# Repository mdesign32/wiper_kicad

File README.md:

# Wiper

Печатная плата контроллера (ATmega, реле), KiCad 9.0.7.

| Файл | Назначение |
|---|---|
| `wiper.kicad_pro` | проект |
| `wiper.kicad_sch` | схема |
| `wiper.kicad_pcb` | печатная плата (2 слоя, 90 × 67,5 мм, 1,6 мм) |

Все символы и посадочные места взяты из стандартных библиотек KiCad 9.

Гербер-файлы изготовленных версий прикладываются к релизам на GitHub.

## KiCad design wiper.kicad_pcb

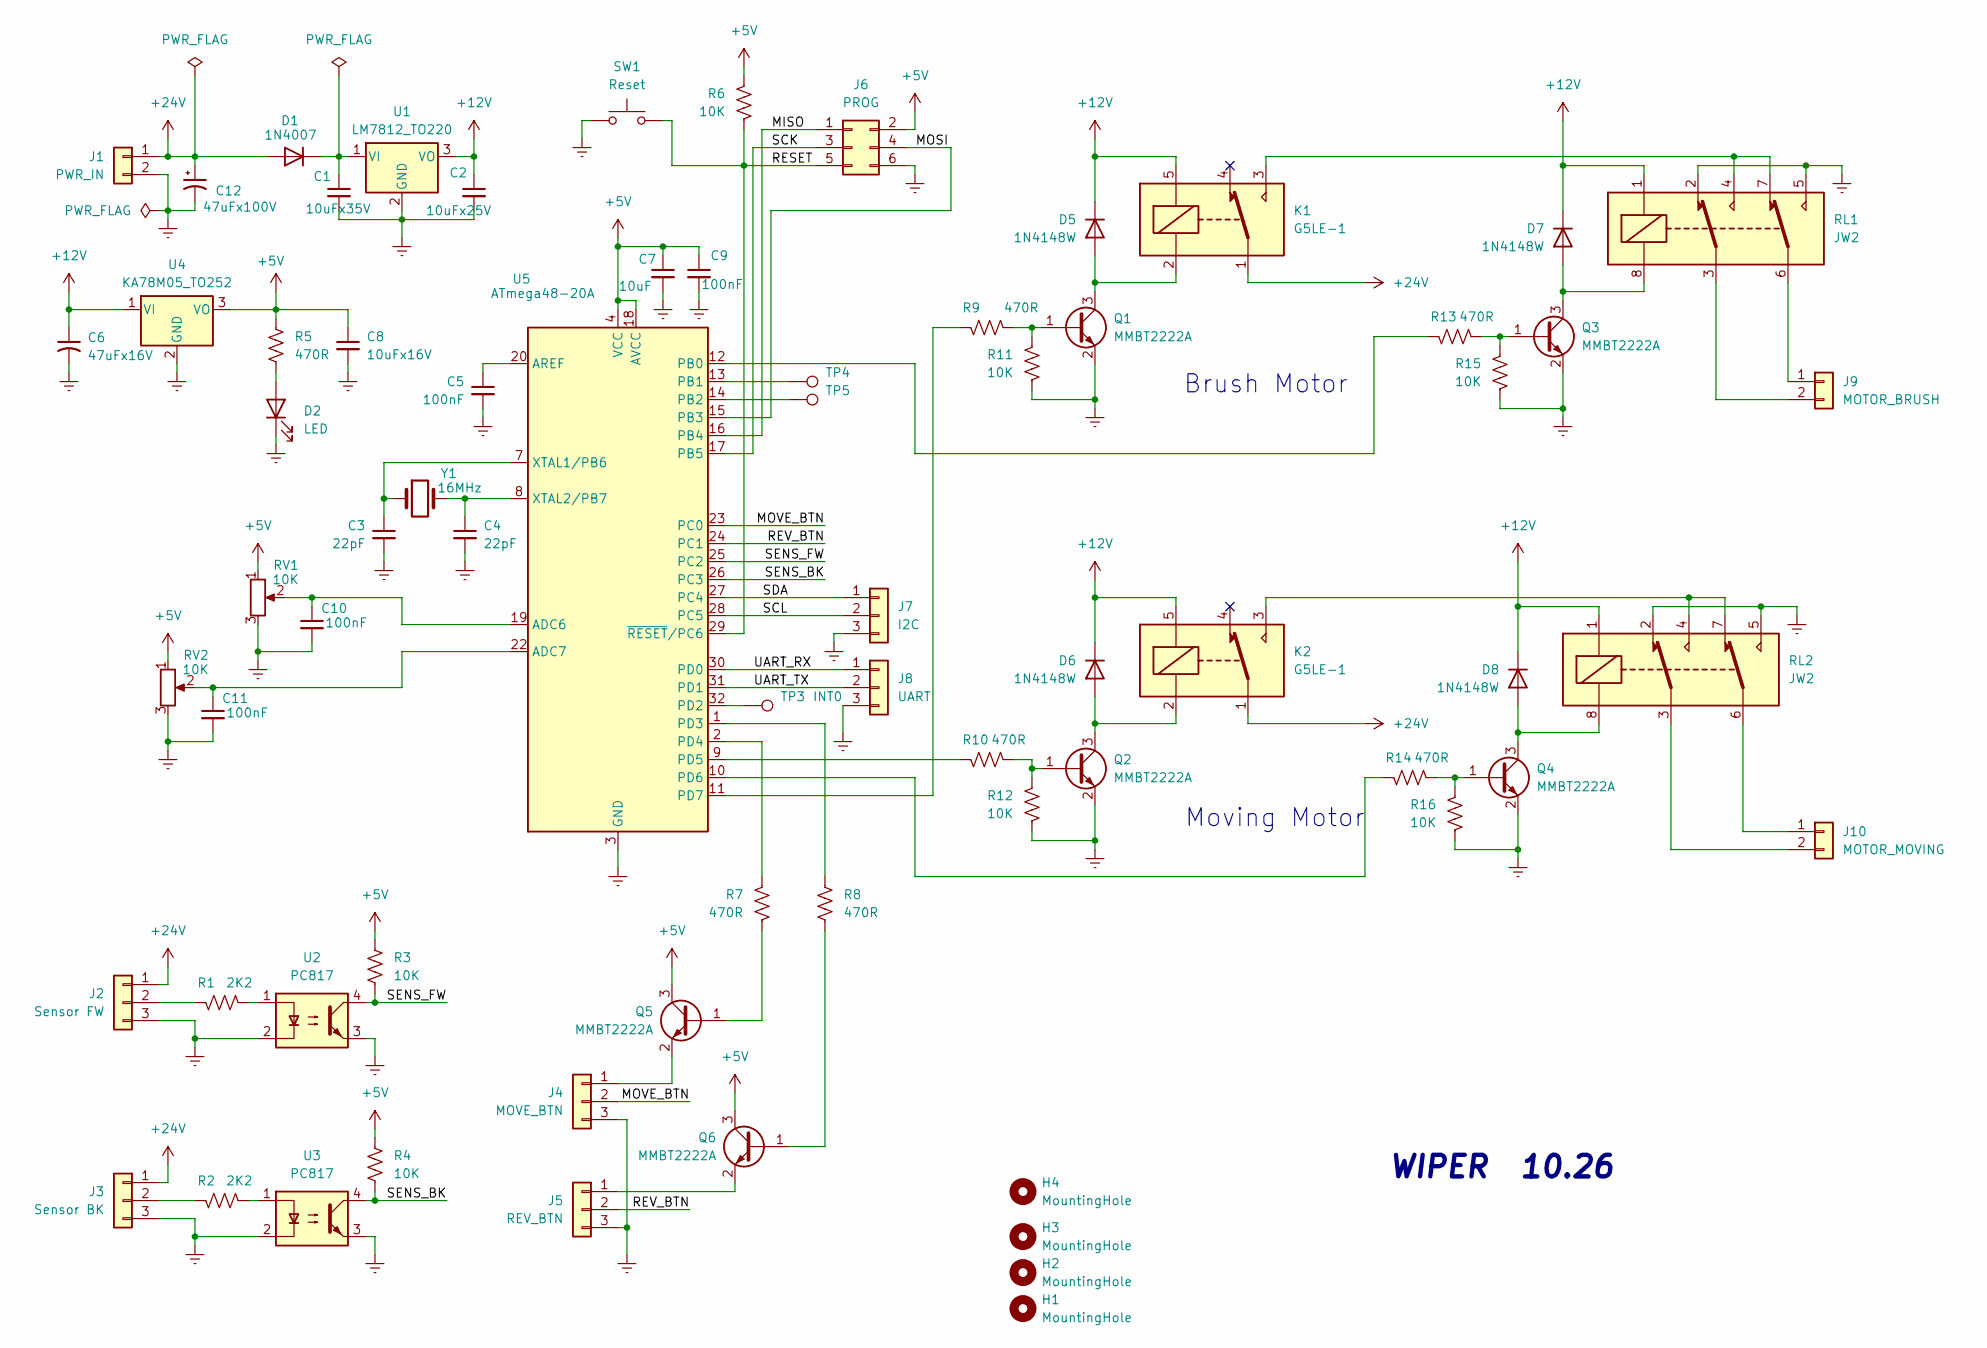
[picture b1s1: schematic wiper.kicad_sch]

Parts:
C1: 10uFx35V; C_1206_3216Metric
C2: 10uFx25V; C_1206_3216Metric
C3, C4: 22pF; C_0603_1608Metric_Pad1.08x0.95mm_HandSolder
C5, C10, C11: 100nF; C_0805_2012Metric_Pad1.18x1.45mm_HandSolder
C6: 47uFx16V; CP_EIA-7132-28_AVX-C_HandSolder
C7: 10uF; C_0805_2012Metric_Pad1.18x1.45mm_HandSolder
C8: 10uFx16V; C_0805_2012Metric_Pad1.18x1.45mm_HandSolder
C9: 100nF; C_0603_1608Metric_Pad1.08x0.95mm_HandSolder
C12: 47uFx100V; C_Radial_D8.0mm_H7.0mm_P3.50mm
D1: 1N4007; D_DO-41_SOD81_P10.16mm_Horizontal
D2: LED; LED_D3.0mm
D5, D6, D7, D8: 1N4148W; D_SOD-123
H1, H2, H3, H4: MountingHole; MountingHole_3.2mm_M3
J1: PWR_IN; TerminalBlock_MetzConnect_Type101_RT01602HBWC_1x02_P5.08mm_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
J2: Sensor FW; TerminalBlock_MetzConnect_Type055_RT01503HDWU_1x03_P5.00mm_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
J3: Sensor BK; TerminalBlock_MetzConnect_Type055_RT01503HDWU_1x03_P5.00mm_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
J4: MOVE_BTN; Molex_KK-254_AE-6410-03A_1x03_P2.54mm_Vertical
J5: REV_BTN; Molex_KK-254_AE-6410-03A_1x03_P2.54mm_Vertical
J6: PROG; PinHeader_2x03_P2.54mm_Vertical
J7: I2C; PinHeader_1x03_P2.54mm_Vertical
J8: UART; PinHeader_1x03_P2.54mm_Vertical
J9: MOTOR_BRUSH; TerminalBlock_MetzConnect_Type101_RT01602HBWC_1x02_P5.08mm_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
J10: MOTOR_MOVING; TerminalBlock_MetzConnect_Type101_RT01602HBWC_1x02_P5.08mm_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
K1, K2: G5LE-1; Relay_SPDT_Omron-G5LE-1
Q1, Q2, Q3, Q4, Q5, Q6: MMBT2222A; SOT-23
R1, R2: 2K2; R_0805_2012Metric_Pad1.20x1.40mm_HandSolder
R3, R4, R6, R11, R12, R15, R16: 10K; R_0805_2012Metric_Pad1.20x1.40mm_HandSolder
R5, R7, R8, R9, R10, R13, R14: 470R; R_0805_2012Metric_Pad1.20x1.40mm_HandSolder
RL1, RL2: JW2; Relay_DPDT_Panasonic_JW2
RV1, RV2: 10K; Potentiometer_Piher_PT-6-V_Vertical
SW1: Reset; SW_Push_1P1T_NO_E-Switch_TL3301NxxxxxG
TP3: INT0; PinHeader_1x01_P1.00mm_Vertical
TP4, TP5: PinHeader_1x01_P1.00mm_Vertical
U1: LM7812_TO220; TO-220-3_Vertical
U2, U3: PC817; DIP-4_W7.62mm
U4: KA78M05_TO252; TO-252-2
U5: ATmega48-20A; TQFP-32_7x7mm_P0.8mm
Y1: 16MHz; Crystal_HC49-4H_Vertical

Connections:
+5V: C7.1, C8.1, C9.1, J6.2, Q5.3 (C), Q6.3 (C), R3.1, R4.1, R5.1, R6.1, RV1.1, RV2.1, U4.3 (VO), U5.4 (VCC), U5.6 (VCC), U5.18 (AVCC)
+12V: C2.1, C6.1, D5.1 (K), D6.1 (K), D7.1 (K), D8.1 (K), K1.5, K2.5, RL1.1, RL2.1, U1.3 (VO), U4.1 (VI)
+24V: C12.1, D1.2 (A), J1.1, J2.1, J3.1, K1.1, K2.1
/MISO: J6.1, U5.16 (PB4)
/MOSI: J6.4, U5.15 (PB3)
/MOVE_BTN: J4.2, U5.23 (PC0)
/RESET: J6.5, R6.2, SW1.2, U5.29 (~RESET/PC6)
/REV_BTN: J5.2, U5.24 (PC1)
/SCK: J6.3, U5.17 (PB5)
/SCL: J7.2, U5.28 (PC5)
/SDA: J7.1, U5.27 (PC4)
/SENS_BK: R4.2, U3.4, U5.26 (PC3)
/SENS_FW: R3.2, U2.4, U5.25 (PC2)
/UART_RX: J8.1, U5.30 (PD0)
/UART_TX: J8.2, U5.31 (PD1)
unnamed: C1.1, D1.1 (K), U1.1 (VI)
unnamed: D2.2 (A), R5.2
unnamed: D5.2 (A), K1.2, Q1.3 (C)
unnamed: D6.2 (A), K2.2, Q2.3 (C)
unnamed: D7.2 (A), Q3.3 (C), RL1.8
unnamed: D8.2 (A), Q4.3 (C), RL2.8
unnamed: J2.2, R1.2
unnamed: J3.2, R2.2
unnamed: J4.1, Q5.2 (E)
unnamed: J5.1, Q6.2 (E)
unnamed: J9.1, RL1.6
unnamed: J9.2, RL1.3
unnamed: J10.1, RL2.6
unnamed: J10.2, RL2.3
unnamed: K1.3, RL1.4, RL1.7
unnamed: K2.3, RL2.4, RL2.7
unnamed: Q1.1 (B), R9.1, R11.1
unnamed: Q2.1 (B), R10.1, R12.1
unnamed: Q3.1 (B), R13.1, R15.1
unnamed: Q4.1 (B), R14.1, R16.1
unnamed: Q5.1 (B), R7.2
unnamed: Q6.1 (B), R8.2
unnamed: R1.1, U2.1
unnamed: R2.1, U3.1
unnamed: C10.1, RV1.2, U5.19 (ADC6)
unnamed: C11.1, RV2.2, U5.22 (ADC7)
unnamed: C5.1, U5.20 (AREF)
unnamed: R13.2, U5.12 (PB0)
unnamed: TP4.1, U5.13 (PB1)
unnamed: TP5.1, U5.14 (PB2)
unnamed: TP3.1, U5.32 (PD2)
unnamed: R8.1, U5.1 (PD3)
unnamed: R7.1, U5.2 (PD4)
unnamed: R10.2, U5.9 (PD5)
unnamed: R14.2, U5.10 (PD6)
unnamed: R9.2, U5.11 (PD7)
unnamed: C3.1, U5.7 (XTAL1/PB6), Y1.1
unnamed: C4.1, U5.8 (XTAL2/PB7), Y1.2
~: C1.2, C2.2, C3.2, C4.2, C5.2, C6.2, C7.2, C8.2, C9.2, C10.2, C11.2, C12.2, D2.1 (K), J1.2, J2.3, J3.3, J4.3, J5.3, J6.6, J7.3, J8.3, Q1.2 (E), Q2.2 (E), Q3.2 (E), Q4.2 (E), R11.2, R12.2, R15.2, R16.2, RL1.2, RL1.5, RL2.2, RL2.5, RV1.3, RV2.3, SW1.1, U1.2 (GND), U2.2, U2.3, U3.2, U3.3, U4.2 (GND), U5.3 (GND), U5.5 (GND), U5.21 (GND)

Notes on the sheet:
Brush Motor
Moving Motor
WIPER 10.26

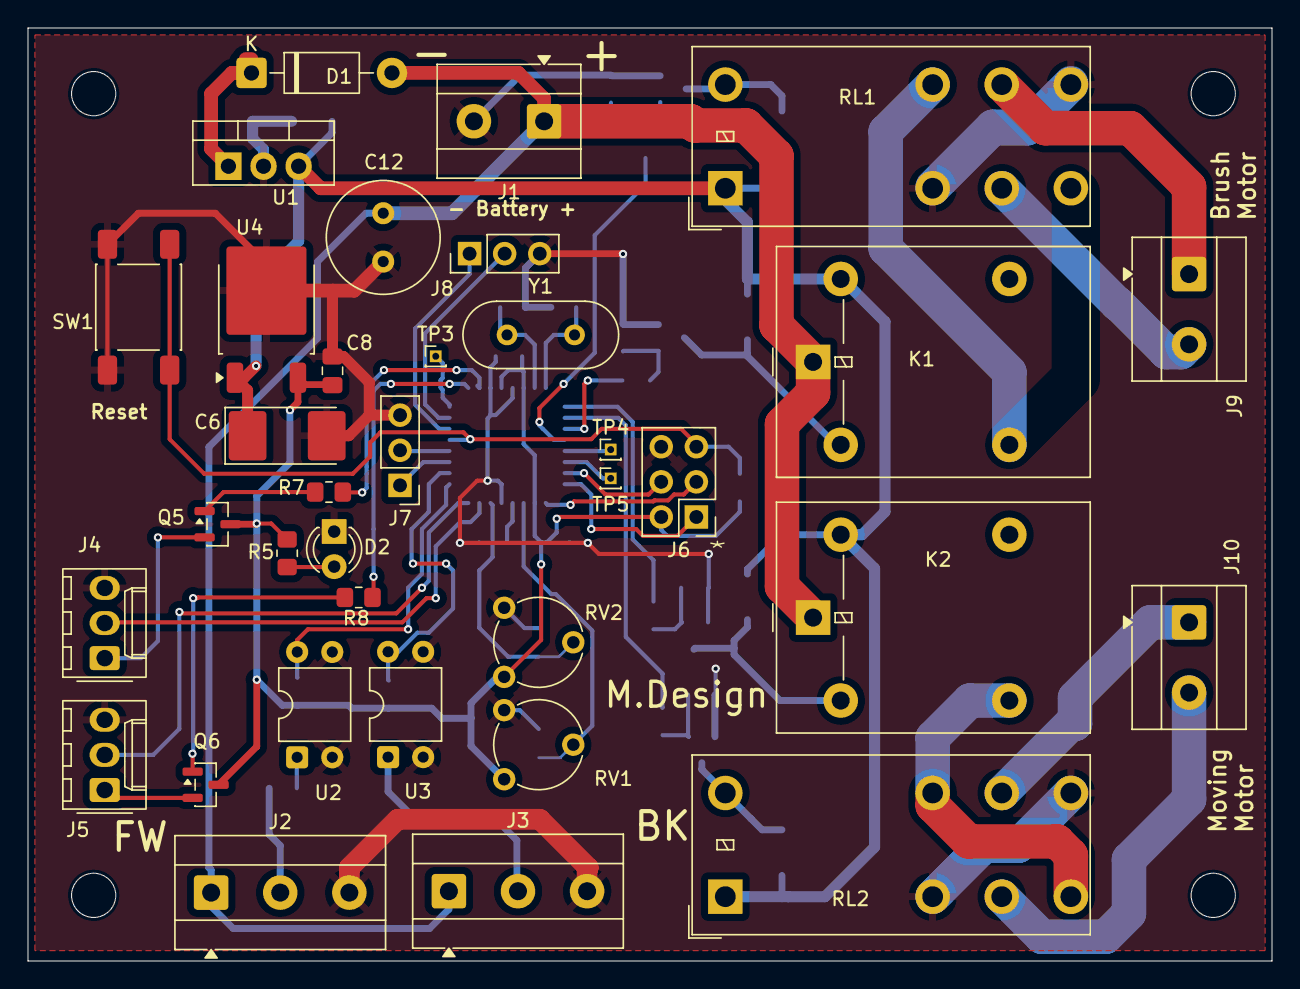
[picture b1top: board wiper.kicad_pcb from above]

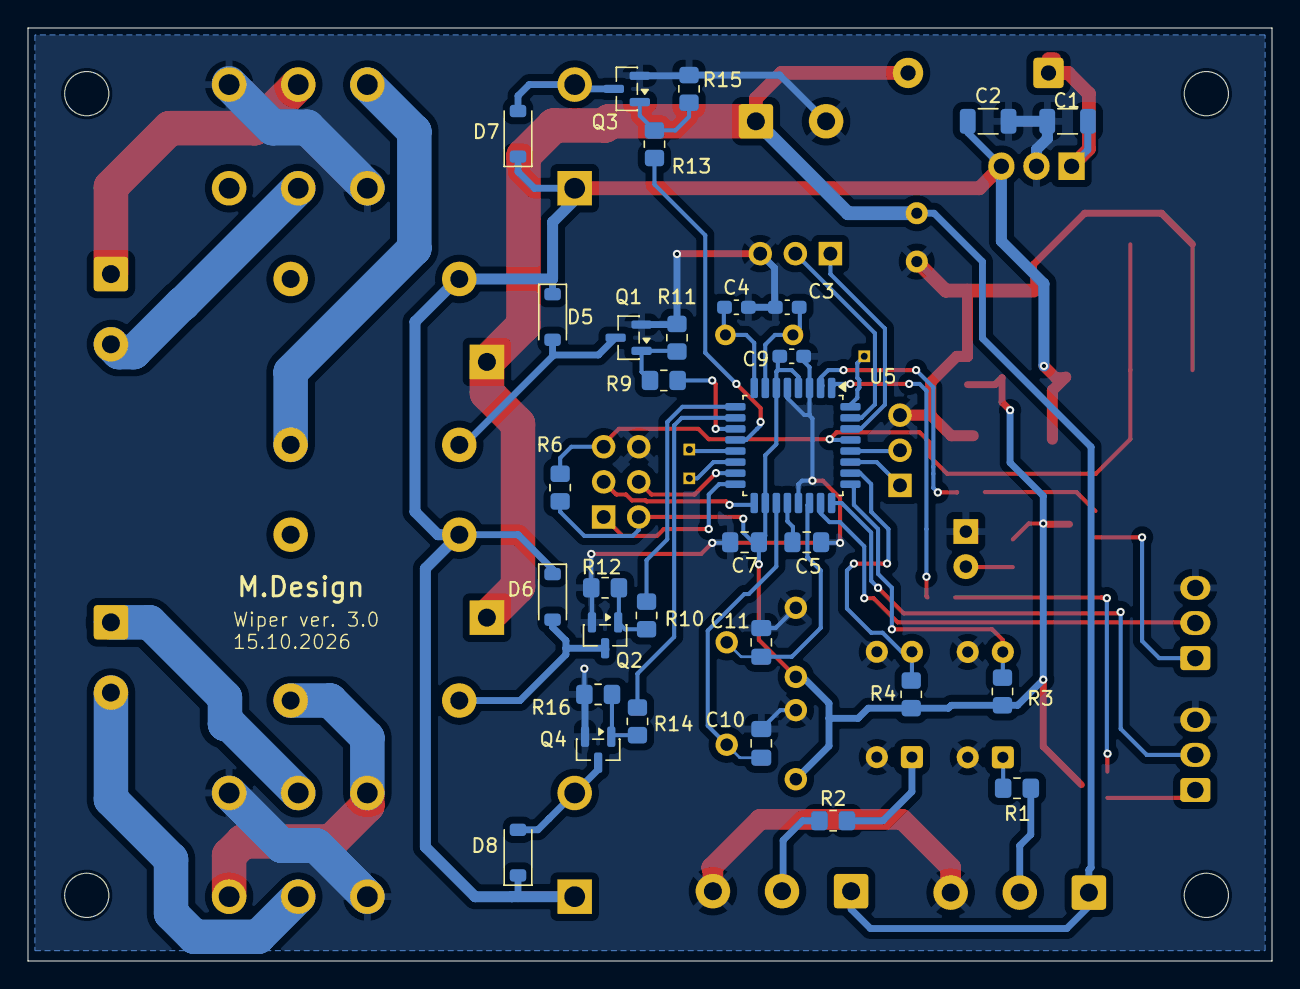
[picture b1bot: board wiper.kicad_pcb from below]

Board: 2 copper layers, 90.0 x 67.5 mm, 70 parts (31 on the bottom side), 54 nets.
